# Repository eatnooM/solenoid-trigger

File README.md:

# solenoid-trigger

License: CC BY-SA 4.0

A simple board to fire a solenoid using an external power supply, without exposing the signal source to the solenoid's power.

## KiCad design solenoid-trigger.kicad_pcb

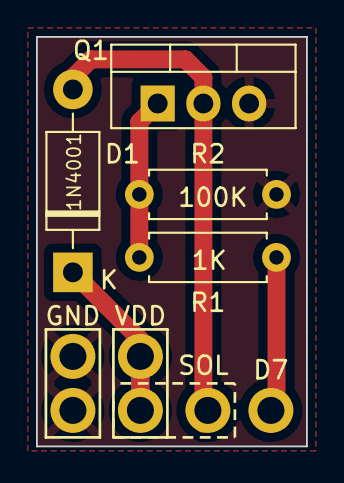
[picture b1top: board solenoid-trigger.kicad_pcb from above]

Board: 2 copper layers, 15.0 x 22.8 mm, 10 parts (0 on the bottom side), 5 nets.

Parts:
D1: 1N4001; D_DO-41_SOD81_P10.16mm_Horizontal
D7: ThroughHole-1.5MM-plated
GND: ThroughHole-1.5MM-plated
GND#2: ThroughHole-1.5MM-plated
L1, L2: ThroughHole-1.5MM-plated
Q1: Q_NMOS_GDS; TO-220-3_Vertical
R1: 1K; R_Axial_DIN0207_L6.3mm_D2.5mm_P7.62mm_Horizontal
R2: 100K; R_Axial_DIN0207_L6.3mm_D2.5mm_P7.62mm_Horizontal
VDD: ThroughHole-1.5MM-plated

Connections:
D7: D7.1, R1.1
GND: GND.1, GND#2.1, Q1.3 (S), R2.1
L2: D1.2 (A), L2.1, Q1.2 (D)
unnamed: Q1.1 (G), R1.2, R2.2
VDD: D1.1 (K), L1.1, VDD.1

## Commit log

2024-02-25 Add readme and license
2024-09-29 Update README.md
    Reflect change to CC BY-SA 4.0 license
